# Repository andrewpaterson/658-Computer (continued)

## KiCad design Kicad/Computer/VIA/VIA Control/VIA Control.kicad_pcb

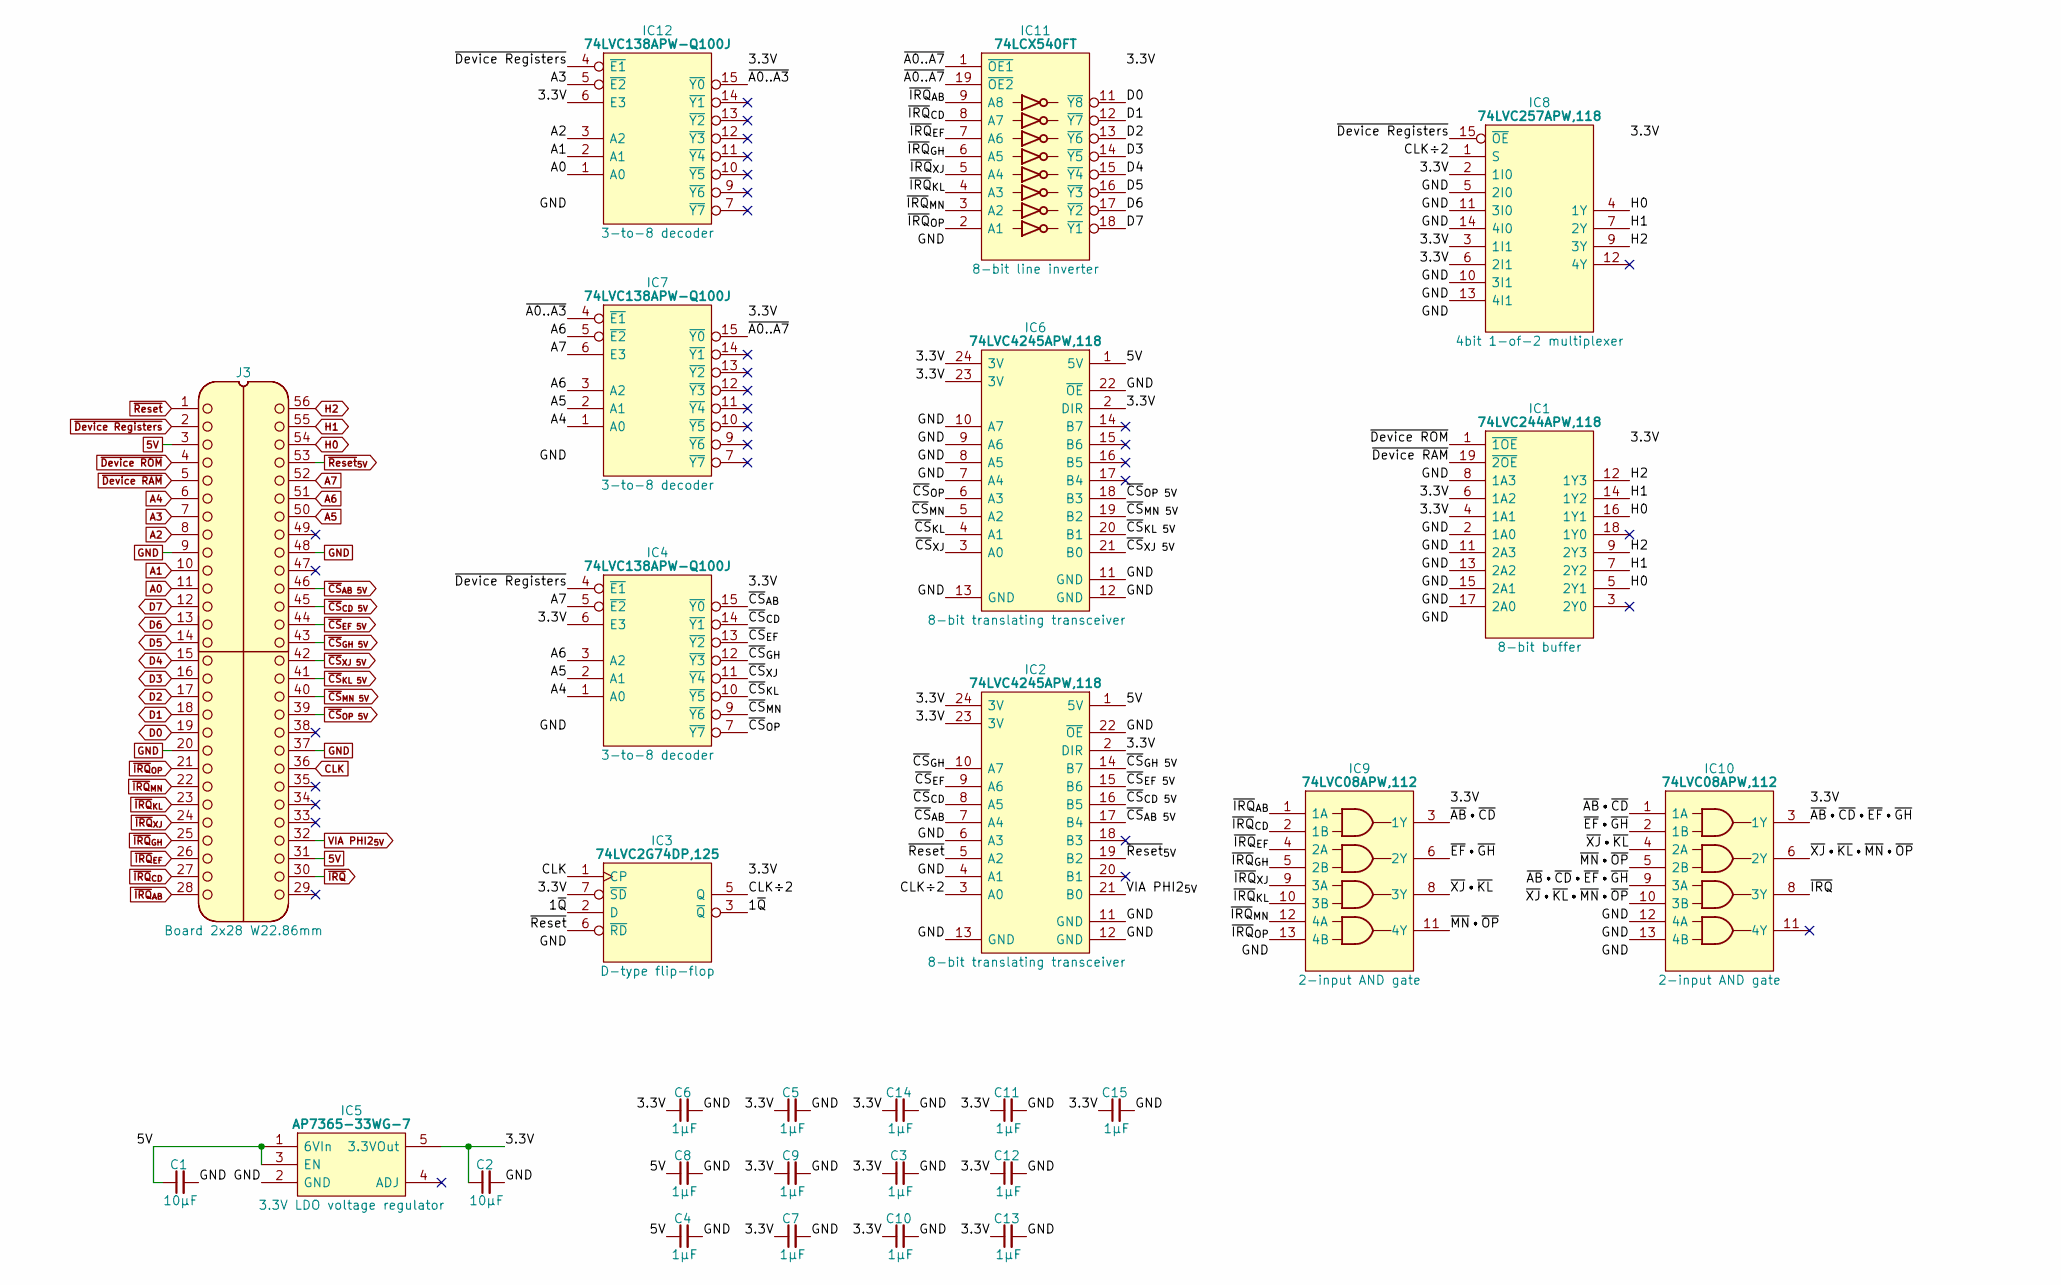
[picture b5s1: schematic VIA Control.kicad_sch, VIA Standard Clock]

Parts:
C1, C2: 10μF; C_0805
C3, C4, C5, C6, C7, C8, C9, C10, C11, C12, C13, C14, C15: 1μF; C_0805
IC1: 74LVC244APW,118; SOP65P640X110-20N; Manufacturer_Part_Number 74LVC244APW,118; Mouser Part Number 771-74LVC244APW-T
IC2, IC6: 74LVC4245APW,118; SOP65P640X110-24N; Mouser Part Number 771-74LVC4245APW-T
IC3: 74LVC2G74DP,125; SOP65P400X110-8N; Manufacturer_Part_Number 74LVC2G74DP,125; Mouser Part Number 771-74LVC2G74DP-G
IC4, IC7, IC12: 74LVC138APW-Q100J; SOP65P640X110-16N; Mouser Part Number 771-74LVC138APWQ100J
IC5: AP7365-33WG-7; SOT95P285X130-5N; Manufacturer_Part_Number AP7365-33WG-7; Mouser Part Number 621-AP7365-33WG-7
IC8: 74LVC257APW,118; SOP65P640X110-16N; Mouser Part Number 771-74LVC257APW-T
IC9, IC10: 74LVC08APW,112; SOP65P640X110-14N; Manufacturer_Part_Number 74LVC08APW,112; Mouser Part Number 771-74LVC08APW
IC11: 74LCX540FT; SOP65P640X120-20N; Manufacturer_Part_Number 74LCX540FT; Mouser Part Number 757-74LCX540FT
J3: Board 2x28 W22.86mm; DIP-56_Board_W22.86mm

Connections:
5V: C1.1, C4.1, C8.1, IC2.1 (5V), IC5.1 (6VIn), IC5.3 (EN), IC6.1 (5V), J3.3, J3.31
/1~Q: IC3.2 (D), IC3.3 (~Q)
/3.3V: C2.1, C3.1, C5.1, C6.1, C7.1, C9.1, C10.1, C11.1, C12.1, C13.1, C14.1, C15.1, IC1.4 (1A1), IC1.6 (1A2), IC1.20 (3V), IC2.2 (DIR), IC2.23 (3V), IC2.24 (3V), IC3.7 (~SD), IC3.8 (3V), IC4.6 (E3), IC4.16 (3V), IC5.5 (3.3VOut), IC6.2 (DIR), IC6.23 (3V), IC6.24 (3V), IC7.16 (3V), IC8.2 (1I0), IC8.3 (1I1), IC8.6 (2I1), IC8.16 (3V), IC9.14 (3V), IC10.14 (3V), IC11.20 (3V), IC12.6 (E3), IC12.16 (3V)
/CLK÷2: IC2.3 (A0), IC3.5 (Q), IC8.1 (S)
/~A0..A3: IC7.4 (~E1), IC12.15 (~Y0)
/~A0..A7: IC7.15 (~Y0), IC11.1 (~OE1), IC11.19 (~OE2)
/~AB•~CD: IC9.3 (1Y), IC10.1 (1A)
/~AB•~CD•~EF•~GH: IC10.3 (1Y), IC10.9 (3A)
/~CS_{AB}: IC2.7 (A4), IC4.15 (~Y0)
/~CS_{CD}: IC2.8 (A5), IC4.14 (~Y1)
/~CS_{EF}: IC2.9 (A6), IC4.13 (~Y2)
/~CS_{GH}: IC2.10 (A7), IC4.12 (~Y3)
/~CS_{KL}: IC4.10 (~Y5), IC6.4 (A1)
/~CS_{MN}: IC4.9 (~Y6), IC6.5 (A2)
/~CS_{OP}: IC4.7 (~Y7), IC6.6 (A3)
/~CS_{XJ}: IC4.11 (~Y4), IC6.3 (A0)
/~EF•~GH: IC9.6 (2Y), IC10.2 (1B)
/~MN•~OP: IC9.11 (4Y), IC10.5 (2B)
/~XJ•~KL: IC9.8 (3Y), IC10.4 (2A)
/~XJ•~KL•~MN•~OP: IC10.6 (2Y), IC10.10 (3B)
A0: IC12.1 (A0), J3.11
A1: IC12.2 (A1), J3.10
A2: IC12.3 (A2), J3.8
A3: IC12.5 (~E2), J3.7
A4: IC4.1 (A0), IC7.1 (A0), J3.6
A5: IC4.2 (A1), IC7.2 (A1), J3.50
A6: IC4.3 (A2), IC7.3 (A2), IC7.5 (~E2), J3.51
A7: IC4.5 (~E2), IC7.6 (E3), J3.52
CLK: IC3.1 (CP), J3.36
D0: IC11.11 (~Y8), J3.19
D1: IC11.12 (~Y7), J3.18
D2: IC11.13 (~Y6), J3.17
D3: IC11.14 (~Y5), J3.16
D4: IC11.15 (~Y4), J3.15
D5: IC11.16 (~Y3), J3.14
D6: IC11.17 (~Y2), J3.13
D7: IC11.18 (~Y1), J3.12
GND: C1.2, C2.2, C3.2, C4.2, C5.2, C6.2, C7.2, C8.2, C9.2, C10.2, C11.2, C12.2, C13.2, C14.2, C15.2, IC1.2 (1A0), IC1.8 (1A3), IC1.10 (GND), IC1.11 (2A3), IC1.13 (2A2), IC1.15 (2A1), IC1.17 (2A0), IC2.4 (A1), IC2.6 (A3), IC2.11 (GND), IC2.12 (GND), IC2.13 (GND), IC2.22 (~OE), IC3.4 (GND), IC4.8 (GND), IC5.2 (GND), IC6.7 (A4), IC6.8 (A5), IC6.9 (A6), IC6.10 (A7), IC6.11 (GND), IC6.12 (GND), IC6.13 (GND), IC6.22 (~OE), IC7.8 (GND), IC8.5 (2I0), IC8.8 (GND), IC8.10 (3I1), IC8.11 (3I0), IC8.13 (4I1), IC8.14 (4I0), IC9.7 (GND), IC10.7 (GND), IC10.12 (4A), IC10.13 (4B), IC11.10 (GND), IC12.8 (GND), J3.9, J3.20, J3.37, J3.48
H0: IC1.5 (2Y1), IC1.16 (1Y1), IC8.4 (1Y), J3.54
H1: IC1.7 (2Y2), IC1.14 (1Y2), IC8.7 (2Y), J3.55
H2: IC1.9 (2Y3), IC1.12 (1Y3), IC8.9 (3Y), J3.56
VIA PHI2_{5V}: IC2.21 (B0), J3.32
~CS_{AB 5V}: IC2.17 (B4), J3.46
~CS_{CD 5V}: IC2.16 (B5), J3.45
~CS_{EF 5V}: IC2.15 (B6), J3.44
~CS_{GH 5V}: IC2.14 (B7), J3.43
~CS_{KL 5V}: IC6.20 (B1), J3.41
~CS_{MN 5V}: IC6.19 (B2), J3.40
~CS_{OP 5V}: IC6.18 (B3), J3.39
~CS_{XJ 5V}: IC6.21 (B0), J3.42
~Device RAM: IC1.19 (~2OE), J3.5
~Device ROM: IC1.1 (~1OE), J3.4
~Device Registers: IC4.4 (~E1), IC8.15 (~OE), IC12.4 (~E1), J3.2
~IRQ: IC10.8 (3Y), J3.30
~IRQ_{AB}: IC9.1 (1A), IC11.9 (A8), J3.28
~IRQ_{CD}: IC9.2 (1B), IC11.8 (A7), J3.27
~IRQ_{EF}: IC9.4 (2A), IC11.7 (A6), J3.26
~IRQ_{GH}: IC9.5 (2B), IC11.6 (A5), J3.25
~IRQ_{KL}: IC9.10 (3B), IC11.4 (A3), J3.23
~IRQ_{MN}: IC9.12 (4A), IC11.3 (A2), J3.22
~IRQ_{OP}: IC9.13 (4B), IC11.2 (A1), J3.21
~IRQ_{XJ}: IC9.9 (3A), IC11.5 (A4), J3.24
~Reset: IC2.5 (A2), IC3.6 (~RD), J3.1
~Reset_{5V}: IC2.19 (B2), J3.53

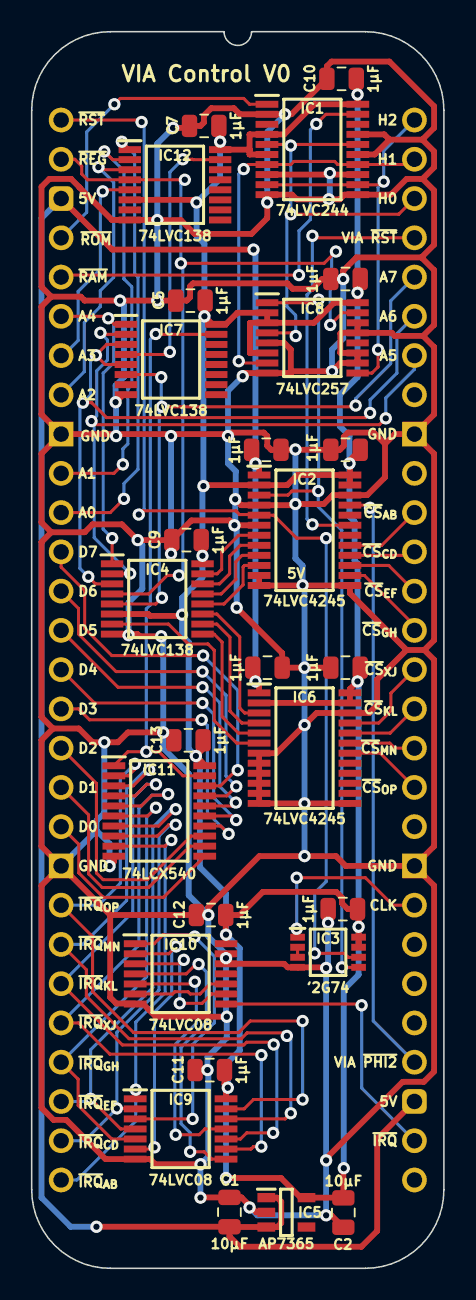
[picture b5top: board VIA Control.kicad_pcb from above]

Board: 2 copper layers, 26.7 x 80.0 mm, 28 parts (0 on the bottom side), 64 nets.

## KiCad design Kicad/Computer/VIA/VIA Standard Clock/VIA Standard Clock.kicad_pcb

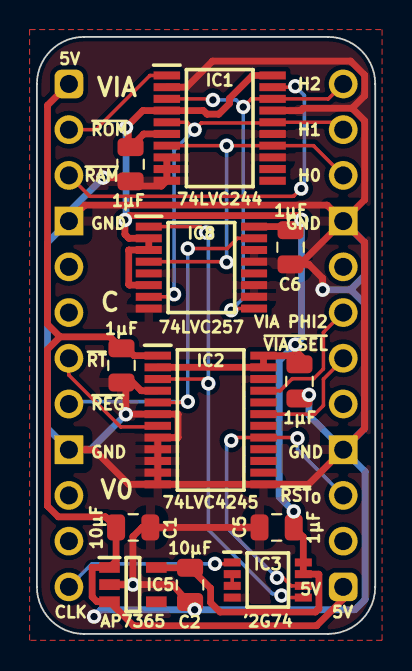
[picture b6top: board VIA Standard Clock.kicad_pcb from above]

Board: 2 copper layers, 18.8 x 33.2 mm, 13 parts (0 on the bottom side), 16 nets.

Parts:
C1, C2: 10μF; C_0805
C3, C5, C6, C8, C9: 1μF; C_0805
IC1: 74LVC244APW,118; SOP65P640X110-20N
IC2: 74LVC4245APW,118; SOP65P640X110-24N
IC3: 74LVC2G74DP,125; SOP65P400X110-8N
IC5: AP7365-33WG-7; SOT95P285X130-5N
IC8: 74LVC257APW,118; SOP65P640X110-16N
J3: Conn_02x16_Counter_Clockwise; DIP-24_Board_W15.24mm

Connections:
/1~Q: IC3.2 (D), IC3.3 (~Q)
/3.3V: C2.1, C3.1, C5.1, C6.1, C9.1, IC1.4 (1A1), IC1.6 (1A2), IC1.20 (3V), IC2.2 (DIR), IC2.23 (3V), IC2.24 (3V), IC3.7 (~SD), IC3.8 (3V), IC5.5 (VOUT), IC8.2 (1I0), IC8.3 (1I1), IC8.6 (2I1), IC8.16 (3V)
/5V: C1.1, C8.1, IC2.1 (5V), IC5.1 (VIN), IC5.3 (EN), J3.1, J3.13
/CLK: IC3.1 (CP), J3.12
/CLK÷2: IC2.3 (A0), IC3.5 (Q), IC8.1 (S)
/GND: C1.2, C2.2, C3.2, C5.2, C6.2, C8.2, C9.2, IC1.2 (1A0), IC1.8 (1A3), IC1.9 (2Y3), IC1.10 (GND), IC1.13 (2A2), IC1.15 (2A1), IC1.17 (2A0), IC2.4 (A1), IC2.6 (A3), IC2.8 (A5), IC2.9 (A6), IC2.10 (A7), IC2.11 (GND), IC2.12 (GND), IC2.13 (GND), IC2.22 (~OE), IC3.4 (GND), IC5.2 (GND), IC8.5 (2I0), IC8.8 (GND), IC8.10 (3I1), IC8.11 (3I0), IC8.13 (4I1), IC8.14 (4I0), J3.4, J3.9, J3.16, J3.21
/H0: IC1.7 (2Y2), IC1.14 (1Y2), IC8.4 (1Y), J3.22
/H1: IC1.5 (2Y1), IC1.16 (1Y1), IC8.7 (2Y), J3.23
/H2: IC1.3 (2Y0), IC1.18 (1Y0), IC8.9 (3Y), J3.24
/VIA PHI2 _{OUT}: IC2.21 (B0), J3.19
/~Device RAM: IC1.19 (~2OE), J3.3
/~Device ROM: IC1.1 (~1OE), J3.2
/~Device Registers: IC2.5 (A2), IC8.15 (~OE), J3.8
/~Reset: IC2.7 (A4), J3.7
/~Reset_{OUT}: IC2.17 (B4), IC3.6 (~RD), J3.15
/~VIA Select _{OUT}: IC2.19 (B2), J3.18
